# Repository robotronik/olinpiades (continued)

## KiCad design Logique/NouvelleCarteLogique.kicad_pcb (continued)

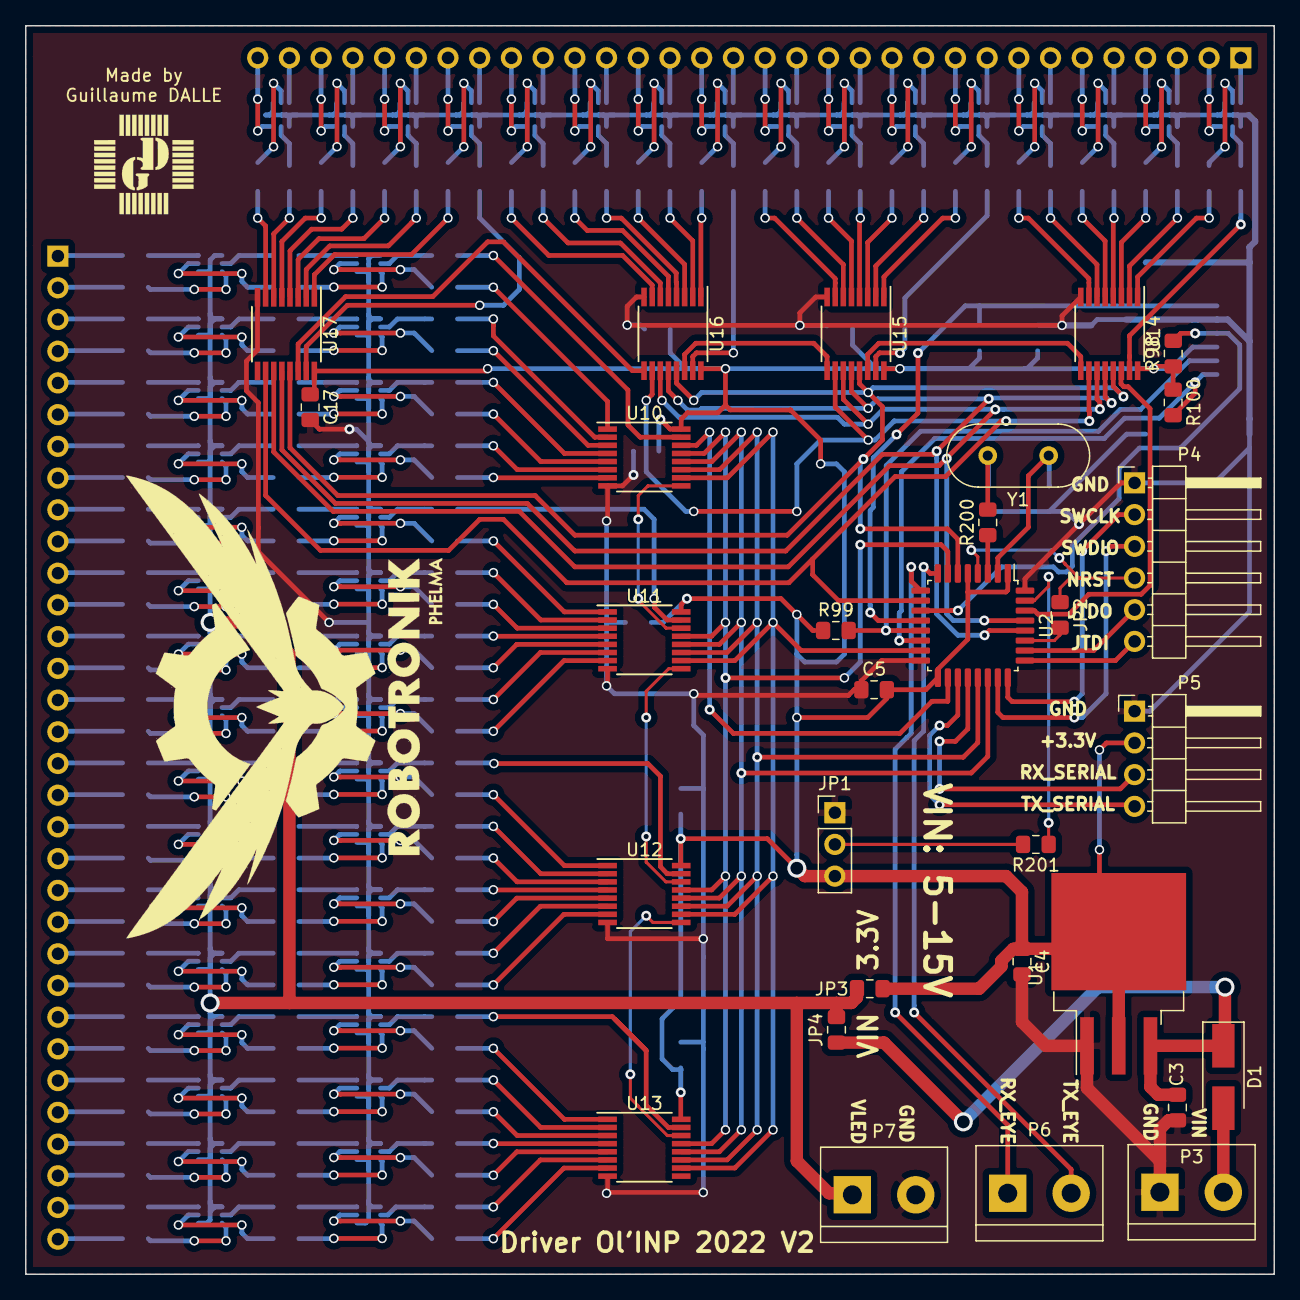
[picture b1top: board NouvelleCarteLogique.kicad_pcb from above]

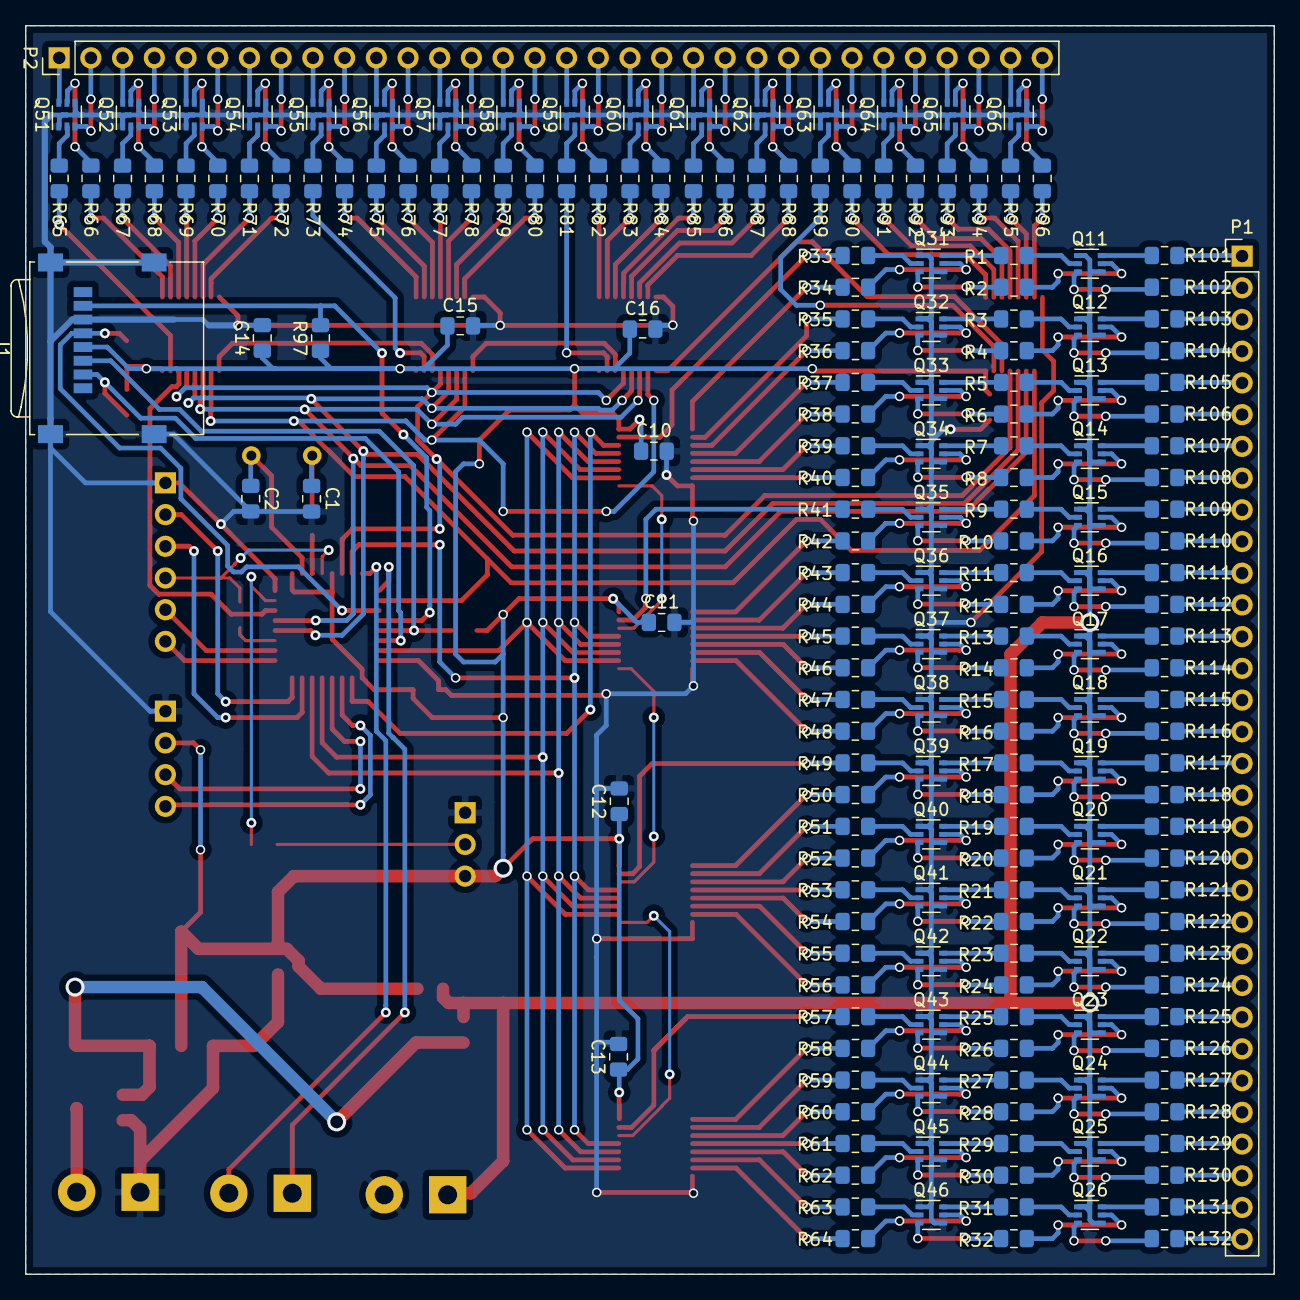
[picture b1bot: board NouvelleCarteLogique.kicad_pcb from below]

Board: 2 copper layers, 100.0 x 100.0 mm, 219 parts (189 on the bottom side), 328 nets.

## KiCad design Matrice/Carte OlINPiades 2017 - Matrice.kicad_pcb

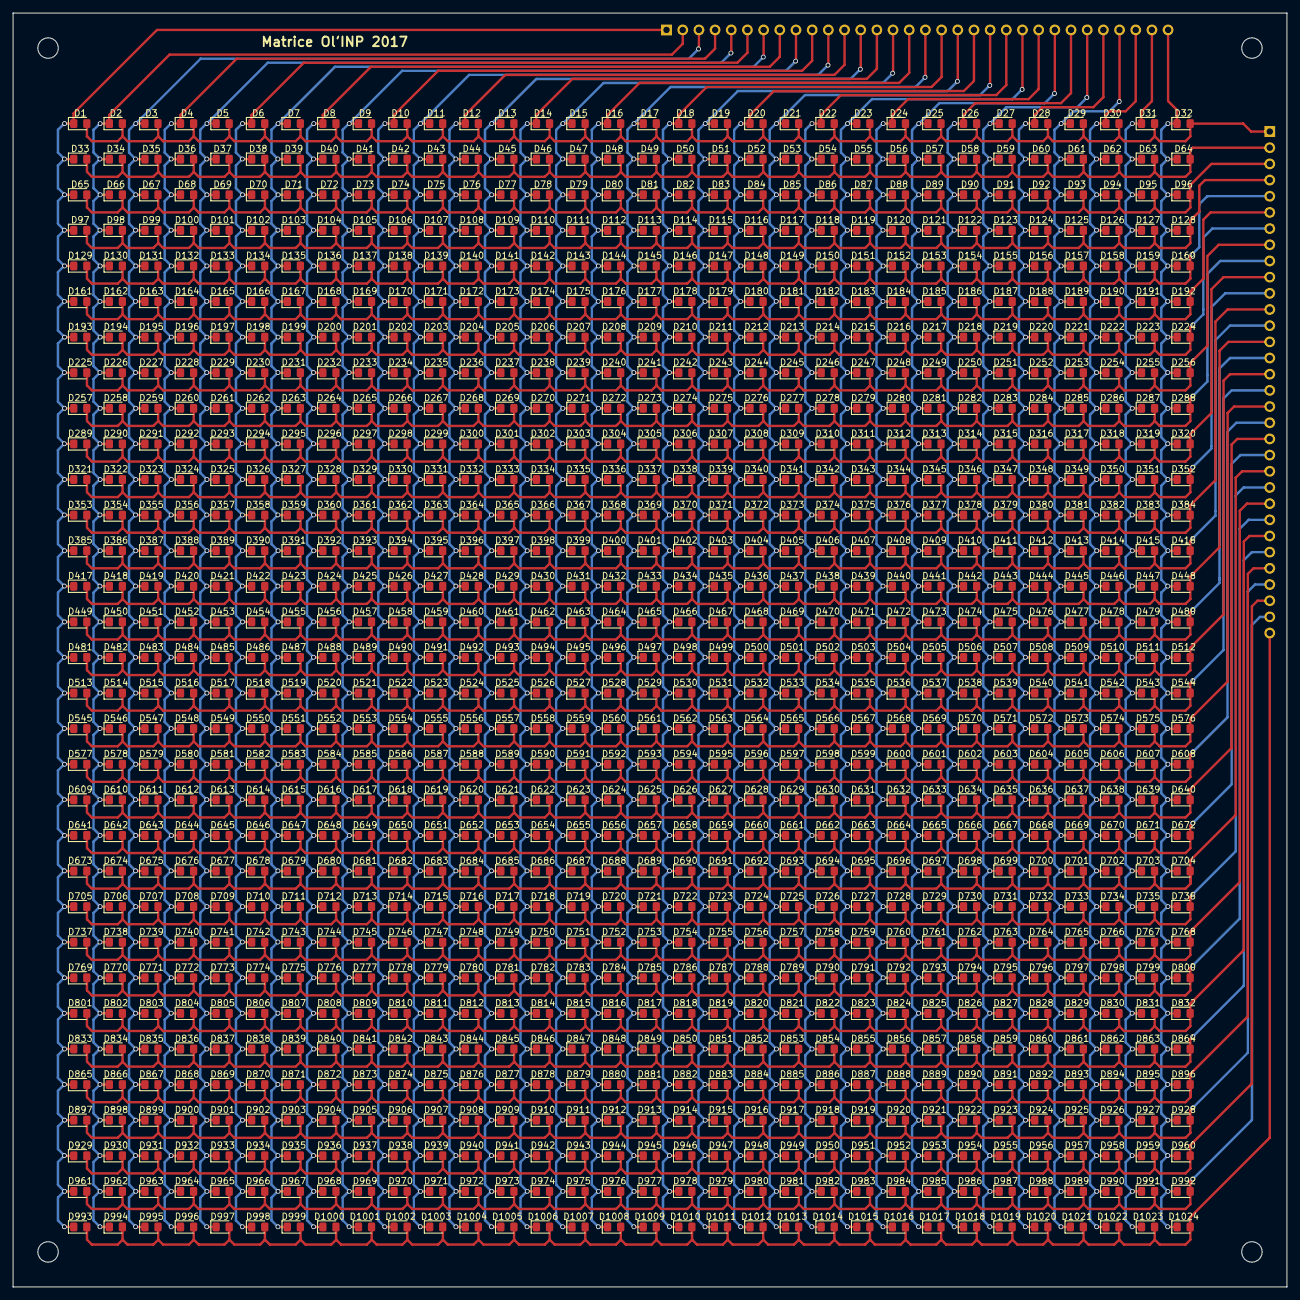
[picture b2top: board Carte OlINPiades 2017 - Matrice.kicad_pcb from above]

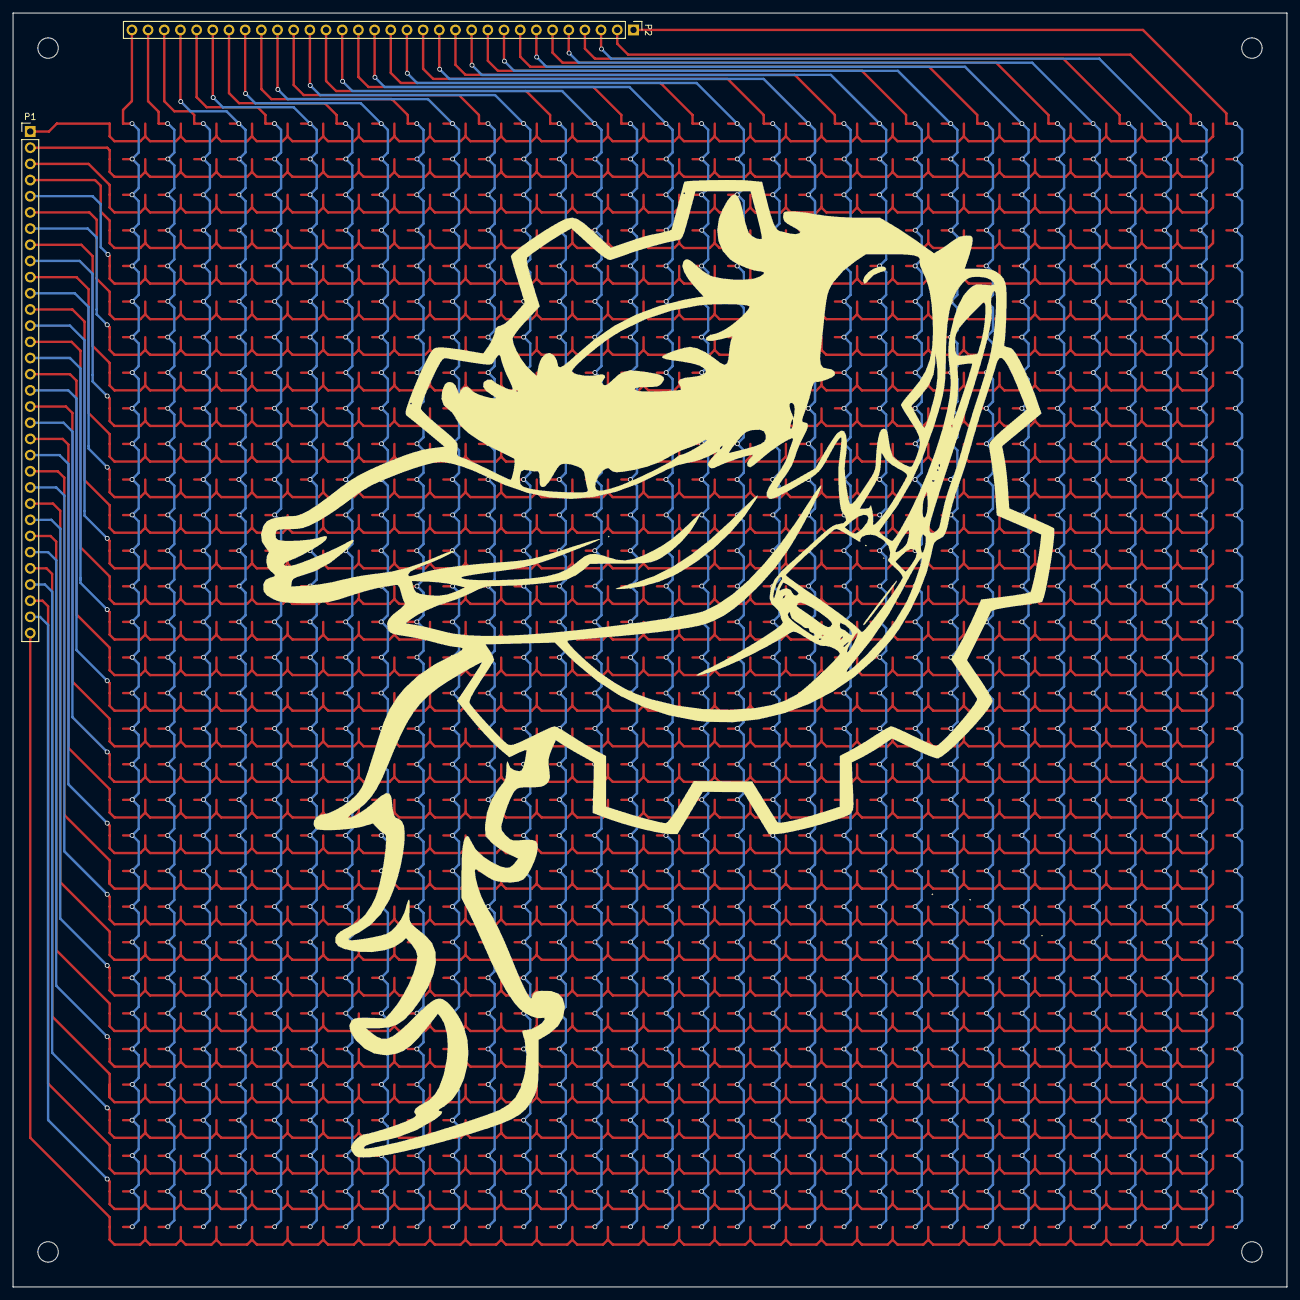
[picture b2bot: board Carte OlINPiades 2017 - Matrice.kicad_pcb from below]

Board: 2 copper layers, 200.0 x 200.0 mm, 1031 parts (3 on the bottom side), 64 nets.

Parts:
D1, D2, D3, D4, D5, D6, D7, D8, D9, D10, D11, D12, D13, D14, D15, D16, D17, D18, D19, D20, D21, D22, D23, D24, D25, D26, D27, D28, D29, D30, D31, D32, D33, D34, D35, D36, D37, D38, D39, D40, D41, D42, D43, D44, D45, D46, D47, D48, D49, D50, D51, D52, D53, D54, D55, D56, D57, D58, D59, D60, D61, D62, D63, D64, D65, D66, D67, D68, D69, D70, D71, D72, D73, D74, D75, D76, D77, D78, D79, D80, D81, D82, D83, D84, D85, D86, D87, D88, D89, D90, D91, D92, D93, D94, D95, D96, D97, D98, D99, D100, D101, D102, D103, D104, D105, D106, D107, D108, D109, D110, D111, D112, D113, D114, D115, D116, D117, D118, D119, D120, D121, D122, D123, D124, D125, D126, D127, D128, D129, D130, D131, D132, D133, D134, D135, D136, D137, D138, D139, D140, D141, D142, D143, D144, D145, D146, D147, D148, D149, D150, D151, D152, D153, D154, D155, D156, D157, D158, D159, D160, D161, D162, D163, D164, D165, D166, D167, D168, D169, D170, D171, D172, D173, D174, D175, D176, D177, D178, D179, D180, D181, D182, D183, D184, D185, D186, D187, D188, D189, D190, D191, D192, D193, D194, D195, D196, D197, D198, D199, D200, D201, D202, D203, D204, D205, D206, D207, D208, D209, D210, D211, D212, D213, D214, D215, D216, D217, D218, D219, D220, D221, D222, D223, D224, D225, D226, D227, D228, D229, D230, D231, D232, D233, D234, D235, D236, D237, D238, D239, D240, D241, D242, D243, D244, D245, D246, D247, D248, D249, D250, D251, D252, D253, D254, D255, D256, D257, D258, D259, D260, D261, D262, D263, D264, D265, D266, D267, D268, D269, D270, D271, D272, D273, D274, D275, D276, D277, D278, D279, D280, D281, D282, D283, D284, D285, D286, D287, D288, D289, D290, D291, D292, D293, D294, D295, D296, D297, D298, D299, D300, D301, D302, D303, D304, D305, D306, D307, D308, D309, D310, D311, D312, D313, D314, D315, D316, D317, D318, D319, D320, D321, D322, D323, D324, D325, D326, D327, D328, D329, D330, D331, D332, D333, D334, D335, D336, D337, D338, D339, D340, D341, D342, D343, D344, D345, D346, D347, D348, D349, D350, D351, D352, D353, D354, D355, D356, D357, D358, D359, D360, D361, D362, D363, D364, D365, D366, D367, D368, D369, D370, D371, D372, D373, D374, D375, D376, D377, D378, D379, D380, D381, D382, D383, D384, D385, D386, D387, D388, D389, D390, D391, D392, D393, D394, D395, D396, D397, D398, D399, D400, D401, D402, D403, D404, D405, D406, D407, D408, D409, D410, D411, D412, D413, D414, D415, D416, D417, D418, D419, D420, D421, D422, D423, D424, D425, D426, D427, D428, D429, D430, D431, D432, D433, D434, D435, D436, D437, D438, D439, D440, D441, D442, D443, D444, D445, D446, D447, D448, D449, D450, D451, D452, D453, D454, D455, D456, D457, D458, D459, D460, D461, D462, D463, D464, D465, D466, D467, D468, D469, D470, D471, D472, D473, D474, D475, D476, D477, D478, D479, D480, D481, D482, D483, D484, D485, D486, D487, D488, D489, D490, D491, D492, D493, D494, D495, D496, D497, D498, D499, D500, D501, D502, D503, D504, D505, D506, D507, D508, D509, D510, D511, D512, D513, D514, D515, D516, D517, D518, D519, D520, D521, D522, D523, D524, D525, D526, D527, D528, D529, D530, D531, D532, D533, D534, D535, D536, D537, D538, D539, D540, D541, D542, D543, D544, D545, D546, D547, D548, D549, D550, D551, D552, D553, D554, D555, D556, D557, D558, D559, D560, D561, D562, D563, D564, D565, D566, D567, D568, D569, D570, D571, D572, D573, D574, D575, D576, D577, D578, D579, D580, D581, D582, D583, D584, D585, D586, D587, D588, D589, D590, D591, D592, D593, D594, D595, D596, D597, D598, D599, D600, D601, D602, D603, D604, D605, D606, D607, D608, D609, D610, D611, D612, D613, D614, D615, D616, D617, D618, D619, D620, D621, D622, D623, D624, D625, D626, D627, D628, D629, D630, D631, D632, D633, D634, D635, D636, D637, D638, D639, D640, D641, D642, D643, D644, D645, D646, D647, D648, D649, D650, D651, D652, D653, D654, D655, D656, D657, D658, D659, D660, D661, D662, D663, D664, D665, D666, D667, D668, D669, D670, D671, D672, D673, D674, D675, D676, D677, D678, D679, D680, D681, D682, D683, D684, D685, D686, D687, D688, D689, D690, D691, D692, D693, D694, D695, D696, D697, D698, D699, D700, D701, D702, D703, D704, D705, D706, D707, D708, D709, D710, D711, D712, D713, D714, D715, D716, D717, D718, D719, D720, D721, D722, D723, D724, D725, D726, D727, D728, D729, D730, D731, D732, D733, D734, D735, D736, D737, D738, D739, D740, D741, D742, D743, D744, D745, D746, D747, D748, D749, D750, D751, D752, D753, D754, D755, D756, D757, D758, D759, D760, D761, D762, D763, D764, D765, D766, D767, D768, D769, D770, D771, D772, D773, D774, D775, D776, D777, D778, D779, D780, D781, D782, D783, D784, D785, D786, D787, D788, D789, D790, D791, D792, D793, D794, D795, D796, D797, D798, D799, D800, D801, D802, D803, D804, D805, D806, D807, D808, D809, D810, D811, D812, D813, D814, D815, D816, D817, D818, D819, D820, D821, D822, D823, D824, D825, D826, D827, D828, D829, D830, D831, D832, D833, D834, D835, D836, D837, D838, D839, D840, D841, D842, D843, D844, D845, D846, D847, D848, D849, D850, D851, D852, D853, D854, D855, D856, D857, D858, D859, D860, D861, D862, D863, D864, D865, D866, D867, D868, D869, D870, D871, D872, D873, D874, D875, D876, D877, D878, D879, D880, D881, D882, D883, D884, D885, D886, D887, D888, D889, D890, D891, D892, D893, D894, D895, D896, D897, D898, D899, D900, D901, D902, D903, D904, D905, D906, D907, D908, D909, D910, D911, D912, D913, D914, D915, D916, D917, D918, D919, D920, D921, D922, D923, D924, D925, D926, D927, D928, D929, D930, D931, D932, D933, D934, D935, D936, D937, D938, D939, D940, D941, D942, D943, D944, D945, D946, D947, D948, D949, D950, D951, D952, D953, D954, D955, D956, D957, D958, D959, D960, D961, D962, D963, D964, D965, D966, D967, D968, D969, D970, D971, D972, D973, D974, D975, D976, D977, D978, D979, D980, D981, D982, D983, D984, D985, D986, D987, D988, D989, D990, D991, D992, D993, D994, D995, D996, D997, D998, D999, D1000, D1001, D1002, D1003, D1004, D1005, D1006, D1007, D1008, D1009, D1010, D1011, D1012, D1013, D1014, D1015, D1016, D1017, D1018, D1019, D1020, D1021, D1022, D1023, D1024: LED; LED_0805_2012Metric_Pad1.15x1.40mm_HandSolder
LOGO1: Logo_Open_Hardware_Small; robotronik_logo_big
P1, P2: CONN_01X32; PinHeader_1x32_P2.54mm_Vertical
PAD1, PAD2, PAD3, PAD4: MountingHole; MountingHole_3.2mm_M3

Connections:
unnamed: D1.1, D33.1, D65.1, D97.1, D129.1, D161.1, D193.1, D225.1, D257.1, D289.1, D321.1, D353.1, D385.1, D417.1, D449.1, D481.1, D513.1, D545.1, D577.1, D609.1, D641.1, D673.1, D705.1, D737.1, D769.1, D801.1, D833.1, D865.1, D897.1, D929.1, D961.1, D993.1, P2.1
unnamed: D1.2, D2.2, D3.2, D4.2, D5.2, D6.2, D7.2, D8.2, D9.2, D10.2, D11.2, D12.2, D13.2, D14.2, D15.2, D16.2, D17.2, D18.2, D19.2, D20.2, D21.2, D22.2, D23.2, D24.2, D25.2, D26.2, D27.2, D28.2, D29.2, D30.2, D31.2, D32.2, P1.1
unnamed: D10.1, D42.1, D74.1, D106.1, D138.1, D170.1, D202.1, D234.1, D266.1, D298.1, D330.1, D362.1, D394.1, D426.1, D458.1, D490.1, D522.1, D554.1, D586.1, D618.1, D650.1, D682.1, D714.1, D746.1, D778.1, D810.1, D842.1, D874.1, D906.1, D938.1, D970.1, D1002.1, P2.10
unnamed: D33.2, D34.2, D35.2, D36.2, D37.2, D38.2, D39.2, D40.2, D41.2, D42.2, D43.2, D44.2, D45.2, D46.2, D47.2, D48.2, D49.2, D50.2, D51.2, D52.2, D53.2, D54.2, D55.2, D56.2, D57.2, D58.2, D59.2, D60.2, D61.2, D62.2, D63.2, D64.2, P1.2
unnamed: D65.2, D66.2, D67.2, D68.2, D69.2, D70.2, D71.2, D72.2, D73.2, D74.2, D75.2, D76.2, D77.2, D78.2, D79.2, D80.2, D81.2, D82.2, D83.2, D84.2, D85.2, D86.2, D87.2, D88.2, D89.2, D90.2, D91.2, D92.2, D93.2, D94.2, D95.2, D96.2, P1.3
unnamed: D4.1, D36.1, D68.1, D100.1, D132.1, D164.1, D196.1, D228.1, D260.1, D292.1, D324.1, D356.1, D388.1, D420.1, D452.1, D484.1, D516.1, D548.1, D580.1, D612.1, D644.1, D676.1, D708.1, D740.1, D772.1, D804.1, D836.1, D868.1, D900.1, D932.1, D964.1, D996.1, P2.4
unnamed: D97.2, D98.2, D99.2, D100.2, D101.2, D102.2, D103.2, D104.2, D105.2, D106.2, D107.2, D108.2, D109.2, D110.2, D111.2, D112.2, D113.2, D114.2, D115.2, D116.2, D117.2, D118.2, D119.2, D120.2, D121.2, D122.2, D123.2, D124.2, D125.2, D126.2, D127.2, D128.2, P1.4
unnamed: D5.1, D37.1, D69.1, D101.1, D133.1, D165.1, D197.1, D229.1, D261.1, D293.1, D325.1, D357.1, D389.1, D421.1, D453.1, D485.1, D517.1, D549.1, D581.1, D613.1, D645.1, D677.1, D709.1, D741.1, D773.1, D805.1, D837.1, D869.1, D901.1, D933.1, D965.1, D997.1, P2.5
unnamed: D6.1, D38.1, D70.1, D102.1, D134.1, D166.1, D198.1, D230.1, D262.1, D294.1, D326.1, D358.1, D390.1, D422.1, D454.1, D486.1, D518.1, D550.1, D582.1, D614.1, D646.1, D678.1, D710.1, D742.1, D774.1, D806.1, D838.1, D870.1, D902.1, D934.1, D966.1, D998.1, P2.6
unnamed: D7.1, D39.1, D71.1, D103.1, D135.1, D167.1, D199.1, D231.1, D263.1, D295.1, D327.1, D359.1, D391.1, D423.1, D455.1, D487.1, D519.1, D551.1, D583.1, D615.1, D647.1, D679.1, D711.1, D743.1, D775.1, D807.1, D839.1, D871.1, D903.1, D935.1, D967.1, D999.1, P2.7
unnamed: D129.2, D130.2, D131.2, D132.2, D133.2, D134.2, D135.2, D136.2, D137.2, D138.2, D139.2, D140.2, D141.2, D142.2, D143.2, D144.2, D145.2, D146.2, D147.2, D148.2, D149.2, D150.2, D151.2, D152.2, D153.2, D154.2, D155.2, D156.2, D157.2, D158.2, D159.2, D160.2, P1.5
unnamed: D2.1, D34.1, D66.1, D98.1, D130.1, D162.1, D194.1, D226.1, D258.1, D290.1, D322.1, D354.1, D386.1, D418.1, D450.1, D482.1, D514.1, D546.1, D578.1, D610.1, D642.1, D674.1, D706.1, D738.1, D770.1, D802.1, D834.1, D866.1, D898.1, D930.1, D962.1, D994.1, P2.2
unnamed: D3.1, D35.1, D67.1, D99.1, D131.1, D163.1, D195.1, D227.1, D259.1, D291.1, D323.1, D355.1, D387.1, D419.1, D451.1, D483.1, D515.1, D547.1, D579.1, D611.1, D643.1, D675.1, D707.1, D739.1, D771.1, D803.1, D835.1, D867.1, D899.1, D931.1, D963.1, D995.1, P2.3
unnamed: D161.2, D162.2, D163.2, D164.2, D165.2, D166.2, D167.2, D168.2, D169.2, D170.2, D171.2, D172.2, D173.2, D174.2, D175.2, D176.2, D177.2, D178.2, D179.2, D180.2, D181.2, D182.2, D183.2, D184.2, D185.2, D186.2, D187.2, D188.2, D189.2, D190.2, D191.2, D192.2, P1.6
unnamed: D193.2, D194.2, D195.2, D196.2, D197.2, D198.2, D199.2, D200.2, D201.2, D202.2, D203.2, D204.2, D205.2, D206.2, D207.2, D208.2, D209.2, D210.2, D211.2, D212.2, D213.2, D214.2, D215.2, D216.2, D217.2, D218.2, D219.2, D220.2, D221.2, D222.2, D223.2, D224.2, P1.7
unnamed: D225.2, D226.2, D227.2, D228.2, D229.2, D230.2, D231.2, D232.2, D233.2, D234.2, D235.2, D236.2, D237.2, D238.2, D239.2, D240.2, D241.2, D242.2, D243.2, D244.2, D245.2, D246.2, D247.2, D248.2, D249.2, D250.2, D251.2, D252.2, D253.2, D254.2, D255.2, D256.2, P1.8
unnamed: D257.2, D258.2, D259.2, D260.2, D261.2, D262.2, D263.2, D264.2, D265.2, D266.2, D267.2, D268.2, D269.2, D270.2, D271.2, D272.2, D273.2, D274.2, D275.2, D276.2, D277.2, D278.2, D279.2, D280.2, D281.2, D282.2, D283.2, D284.2, D285.2, D286.2, D287.2, D288.2, P1.9
unnamed: D289.2, D290.2, D291.2, D292.2, D293.2, D294.2, D295.2, D296.2, D297.2, D298.2, D299.2, D300.2, D301.2, D302.2, D303.2, D304.2, D305.2, D306.2, D307.2, D308.2, D309.2, D310.2, D311.2, D312.2, D313.2, D314.2, D315.2, D316.2, D317.2, D318.2, D319.2, D320.2, P1.10
unnamed: D321.2, D322.2, D323.2, D324.2, D325.2, D326.2, D327.2, D328.2, D329.2, D330.2, D331.2, D332.2, D333.2, D334.2, D335.2, D336.2, D337.2, D338.2, D339.2, D340.2, D341.2, D342.2, D343.2, D344.2, D345.2, D346.2, D347.2, D348.2, D349.2, D350.2, D351.2, D352.2, P1.11
unnamed: D353.2, D354.2, D355.2, D356.2, D357.2, D358.2, D359.2, D360.2, D361.2, D362.2, D363.2, D364.2, D365.2, D366.2, D367.2, D368.2, D369.2, D370.2, D371.2, D372.2, D373.2, D374.2, D375.2, D376.2, D377.2, D378.2, D379.2, D380.2, D381.2, D382.2, D383.2, D384.2, P1.12
unnamed: D385.2, D386.2, D387.2, D388.2, D389.2, D390.2, D391.2, D392.2, D393.2, D394.2, D395.2, D396.2, D397.2, D398.2, D399.2, D400.2, D401.2, D402.2, D403.2, D404.2, D405.2, D406.2, D407.2, D408.2, D409.2, D410.2, D411.2, D412.2, D413.2, D414.2, D415.2, D416.2, P1.13
unnamed: D417.2, D418.2, D419.2, D420.2, D421.2, D422.2, D423.2, D424.2, D425.2, D426.2, D427.2, D428.2, D429.2, D430.2, D431.2, D432.2, D433.2, D434.2, D435.2, D436.2, D437.2, D438.2, D439.2, D440.2, D441.2, D442.2, D443.2, D444.2, D445.2, D446.2, D447.2, D448.2, P1.14
unnamed: D449.2, D450.2, D451.2, D452.2, D453.2, D454.2, D455.2, D456.2, D457.2, D458.2, D459.2, D460.2, D461.2, D462.2, D463.2, D464.2, D465.2, D466.2, D467.2, D468.2, D469.2, D470.2, D471.2, D472.2, D473.2, D474.2, D475.2, D476.2, D477.2, D478.2, D479.2, D480.2, P1.15
unnamed: D481.2, D482.2, D483.2, D484.2, D485.2, D486.2, D487.2, D488.2, D489.2, D490.2, D491.2, D492.2, D493.2, D494.2, D495.2, D496.2, D497.2, D498.2, D499.2, D500.2, D501.2, D502.2, D503.2, D504.2, D505.2, D506.2, D507.2, D508.2, D509.2, D510.2, D511.2, D512.2, P1.16
unnamed: D513.2, D514.2, D515.2, D516.2, D517.2, D518.2, D519.2, D520.2, D521.2, D522.2, D523.2, D524.2, D525.2, D526.2, D527.2, D528.2, D529.2, D530.2, D531.2, D532.2, D533.2, D534.2, D535.2, D536.2, D537.2, D538.2, D539.2, D540.2, D541.2, D542.2, D543.2, D544.2, P1.17
unnamed: D545.2, D546.2, D547.2, D548.2, D549.2, D550.2, D551.2, D552.2, D553.2, D554.2, D555.2, D556.2, D557.2, D558.2, D559.2, D560.2, D561.2, D562.2, D563.2, D564.2, D565.2, D566.2, D567.2, D568.2, D569.2, D570.2, D571.2, D572.2, D573.2, D574.2, D575.2, D576.2, P1.18
unnamed: D577.2, D578.2, D579.2, D580.2, D581.2, D582.2, D583.2, D584.2, D585.2, D586.2, D587.2, D588.2, D589.2, D590.2, D591.2, D592.2, D593.2, D594.2, D595.2, D596.2, D597.2, D598.2, D599.2, D600.2, D601.2, D602.2, D603.2, D604.2, D605.2, D606.2, D607.2, D608.2, P1.19
unnamed: D609.2, D610.2, D611.2, D612.2, D613.2, D614.2, D615.2, D616.2, D617.2, D618.2, D619.2, D620.2, D621.2, D622.2, D623.2, D624.2, D625.2, D626.2, D627.2, D628.2, D629.2, D630.2, D631.2, D632.2, D633.2, D634.2, D635.2, D636.2, D637.2, D638.2, D639.2, D640.2, P1.20
unnamed: D641.2, D642.2, D643.2, D644.2, D645.2, D646.2, D647.2, D648.2, D649.2, D650.2, D651.2, D652.2, D653.2, D654.2, D655.2, D656.2, D657.2, D658.2, D659.2, D660.2, D661.2, D662.2, D663.2, D664.2, D665.2, D666.2, D667.2, D668.2, D669.2, D670.2, D671.2, D672.2, P1.21
unnamed: D673.2, D674.2, D675.2, D676.2, D677.2, D678.2, D679.2, D680.2, D681.2, D682.2, D683.2, D684.2, D685.2, D686.2, D687.2, D688.2, D689.2, D690.2, D691.2, D692.2, D693.2, D694.2, D695.2, D696.2, D697.2, D698.2, D699.2, D700.2, D701.2, D702.2, D703.2, D704.2, P1.22
unnamed: D705.2, D706.2, D707.2, D708.2, D709.2, D710.2, D711.2, D712.2, D713.2, D714.2, D715.2, D716.2, D717.2, D718.2, D719.2, D720.2, D721.2, D722.2, D723.2, D724.2, D725.2, D726.2, D727.2, D728.2, D729.2, D730.2, D731.2, D732.2, D733.2, D734.2, D735.2, D736.2, P1.23
unnamed: D737.2, D738.2, D739.2, D740.2, D741.2, D742.2, D743.2, D744.2, D745.2, D746.2, D747.2, D748.2, D749.2, D750.2, D751.2, D752.2, D753.2, D754.2, D755.2, D756.2, D757.2, D758.2, D759.2, D760.2, D761.2, D762.2, D763.2, D764.2, D765.2, D766.2, D767.2, D768.2, P1.24
unnamed: D769.2, D770.2, D771.2, D772.2, D773.2, D774.2, D775.2, D776.2, D777.2, D778.2, D779.2, D780.2, D781.2, D782.2, D783.2, D784.2, D785.2, D786.2, D787.2, D788.2, D789.2, D790.2, D791.2, D792.2, D793.2, D794.2, D795.2, D796.2, D797.2, D798.2, D799.2, D800.2, P1.25
unnamed: D801.2, D802.2, D803.2, D804.2, D805.2, D806.2, D807.2, D808.2, D809.2, D810.2, D811.2, D812.2, D813.2, D814.2, D815.2, D816.2, D817.2, D818.2, D819.2, D820.2, D821.2, D822.2, D823.2, D824.2, D825.2, D826.2, D827.2, D828.2, D829.2, D830.2, D831.2, D832.2, P1.26
unnamed: D833.2, D834.2, D835.2, D836.2, D837.2, D838.2, D839.2, D840.2, D841.2, D842.2, D843.2, D844.2, D845.2, D846.2, D847.2, D848.2, D849.2, D850.2, D851.2, D852.2, D853.2, D854.2, D855.2, D856.2, D857.2, D858.2, D859.2, D860.2, D861.2, D862.2, D863.2, D864.2, P1.27
unnamed: D865.2, D866.2, D867.2, D868.2, D869.2, D870.2, D871.2, D872.2, D873.2, D874.2, D875.2, D876.2, D877.2, D878.2, D879.2, D880.2, D881.2, D882.2, D883.2, D884.2, D885.2, D886.2, D887.2, D888.2, D889.2, D890.2, D891.2, D892.2, D893.2, D894.2, D895.2, D896.2, P1.28
unnamed: D897.2, D898.2, D899.2, D900.2, D901.2, D902.2, D903.2, D904.2, D905.2, D906.2, D907.2, D908.2, D909.2, D910.2, D911.2, D912.2, D913.2, D914.2, D915.2, D916.2, D917.2, D918.2, D919.2, D920.2, D921.2, D922.2, D923.2, D924.2, D925.2, D926.2, D927.2, D928.2, P1.29
unnamed: D929.2, D930.2, D931.2, D932.2, D933.2, D934.2, D935.2, D936.2, D937.2, D938.2, D939.2, D940.2, D941.2, D942.2, D943.2, D944.2, D945.2, D946.2, D947.2, D948.2, D949.2, D950.2, D951.2, D952.2, D953.2, D954.2, D955.2, D956.2, D957.2, D958.2, D959.2, D960.2, P1.30
unnamed: D961.2, D962.2, D963.2, D964.2, D965.2, D966.2, D967.2, D968.2, D969.2, D970.2, D971.2, D972.2, D973.2, D974.2, D975.2, D976.2, D977.2, D978.2, D979.2, D980.2, D981.2, D982.2, D983.2, D984.2, D985.2, D986.2, D987.2, D988.2, D989.2, D990.2, D991.2, D992.2, P1.31
unnamed: D8.1, D40.1, D72.1, D104.1, D136.1, D168.1, D200.1, D232.1, D264.1, D296.1, D328.1, D360.1, D392.1, D424.1, D456.1, D488.1, D520.1, D552.1, D584.1, D616.1, D648.1, D680.1, D712.1, D744.1, D776.1, D808.1, D840.1, D872.1, D904.1, D936.1, D968.1, D1000.1, P2.8
unnamed: D993.2, D994.2, D995.2, D996.2, D997.2, D998.2, D999.2, D1000.2, D1001.2, D1002.2, D1003.2, D1004.2, D1005.2, D1006.2, D1007.2, D1008.2, D1009.2, D1010.2, D1011.2, D1012.2, D1013.2, D1014.2, D1015.2, D1016.2, D1017.2, D1018.2, D1019.2, D1020.2, D1021.2, D1022.2, D1023.2, D1024.2, P1.32
unnamed: D9.1, D41.1, D73.1, D105.1, D137.1, D169.1, D201.1, D233.1, D265.1, D297.1, D329.1, D361.1, D393.1, D425.1, D457.1, D489.1, D521.1, D553.1, D585.1, D617.1, D649.1, D681.1, D713.1, D745.1, D777.1, D809.1, D841.1, D873.1, D905.1, D937.1, D969.1, D1001.1, P2.9
unnamed: D11.1, D43.1, D75.1, D107.1, D139.1, D171.1, D203.1, D235.1, D267.1, D299.1, D331.1, D363.1, D395.1, D427.1, D459.1, D491.1, D523.1, D555.1, D587.1, D619.1, D651.1, D683.1, D715.1, D747.1, D779.1, D811.1, D843.1, D875.1, D907.1, D939.1, D971.1, D1003.1, P2.11
unnamed: D12.1, D44.1, D76.1, D108.1, D140.1, D172.1, D204.1, D236.1, D268.1, D300.1, D332.1, D364.1, D396.1, D428.1, D460.1, D492.1, D524.1, D556.1, D588.1, D620.1, D652.1, D684.1, D716.1, D748.1, D780.1, D812.1, D844.1, D876.1, D908.1, D940.1, D972.1, D1004.1, P2.12
unnamed: D13.1, D45.1, D77.1, D109.1, D141.1, D173.1, D205.1, D237.1, D269.1, D301.1, D333.1, D365.1, D397.1, D429.1, D461.1, D493.1, D525.1, D557.1, D589.1, D621.1, D653.1, D685.1, D717.1, D749.1, D781.1, D813.1, D845.1, D877.1, D909.1, D941.1, D973.1, D1005.1, P2.13
unnamed: D14.1, D46.1, D78.1, D110.1, D142.1, D174.1, D206.1, D238.1, D270.1, D302.1, D334.1, D366.1, D398.1, D430.1, D462.1, D494.1, D526.1, D558.1, D590.1, D622.1, D654.1, D686.1, D718.1, D750.1, D782.1, D814.1, D846.1, D878.1, D910.1, D942.1, D974.1, D1006.1, P2.14
unnamed: D15.1, D47.1, D79.1, D111.1, D143.1, D175.1, D207.1, D239.1, D271.1, D303.1, D335.1, D367.1, D399.1, D431.1, D463.1, D495.1, D527.1, D559.1, D591.1, D623.1, D655.1, D687.1, D719.1, D751.1, D783.1, D815.1, D847.1, D879.1, D911.1, D943.1, D975.1, D1007.1, P2.15
unnamed: D16.1, D48.1, D80.1, D112.1, D144.1, D176.1, D208.1, D240.1, D272.1, D304.1, D336.1, D368.1, D400.1, D432.1, D464.1, D496.1, D528.1, D560.1, D592.1, D624.1, D656.1, D688.1, D720.1, D752.1, D784.1, D816.1, D848.1, D880.1, D912.1, D944.1, D976.1, D1008.1, P2.16
unnamed: D17.1, D49.1, D81.1, D113.1, D145.1, D177.1, D209.1, D241.1, D273.1, D305.1, D337.1, D369.1, D401.1, D433.1, D465.1, D497.1, D529.1, D561.1, D593.1, D625.1, D657.1, D689.1, D721.1, D753.1, D785.1, D817.1, D849.1, D881.1, D913.1, D945.1, D977.1, D1009.1, P2.17
unnamed: D18.1, D50.1, D82.1, D114.1, D146.1, D178.1, D210.1, D242.1, D274.1, D306.1, D338.1, D370.1, D402.1, D434.1, D466.1, D498.1, D530.1, D562.1, D594.1, D626.1, D658.1, D690.1, D722.1, D754.1, D786.1, D818.1, D850.1, D882.1, D914.1, D946.1, D978.1, D1010.1, P2.18
unnamed: D19.1, D51.1, D83.1, D115.1, D147.1, D179.1, D211.1, D243.1, D275.1, D307.1, D339.1, D371.1, D403.1, D435.1, D467.1, D499.1, D531.1, D563.1, D595.1, D627.1, D659.1, D691.1, D723.1, D755.1, D787.1, D819.1, D851.1, D883.1, D915.1, D947.1, D979.1, D1011.1, P2.19
unnamed: D20.1, D52.1, D84.1, D116.1, D148.1, D180.1, D212.1, D244.1, D276.1, D308.1, D340.1, D372.1, D404.1, D436.1, D468.1, D500.1, D532.1, D564.1, D596.1, D628.1, D660.1, D692.1, D724.1, D756.1, D788.1, D820.1, D852.1, D884.1, D916.1, D948.1, D980.1, D1012.1, P2.20
unnamed: D21.1, D53.1, D85.1, D117.1, D149.1, D181.1, D213.1, D245.1, D277.1, D309.1, D341.1, D373.1, D405.1, D437.1, D469.1, D501.1, D533.1, D565.1, D597.1, D629.1, D661.1, D693.1, D725.1, D757.1, D789.1, D821.1, D853.1, D885.1, D917.1, D949.1, D981.1, D1013.1, P2.21
unnamed: D22.1, D54.1, D86.1, D118.1, D150.1, D182.1, D214.1, D246.1, D278.1, D310.1, D342.1, D374.1, D406.1, D438.1, D470.1, D502.1, D534.1, D566.1, D598.1, D630.1, D662.1, D694.1, D726.1, D758.1, D790.1, D822.1, D854.1, D886.1, D918.1, D950.1, D982.1, D1014.1, P2.22
unnamed: D23.1, D55.1, D87.1, D119.1, D151.1, D183.1, D215.1, D247.1, D279.1, D311.1, D343.1, D375.1, D407.1, D439.1, D471.1, D503.1, D535.1, D567.1, D599.1, D631.1, D663.1, D695.1, D727.1, D759.1, D791.1, D823.1, D855.1, D887.1, D919.1, D951.1, D983.1, D1015.1, P2.23
unnamed: D24.1, D56.1, D88.1, D120.1, D152.1, D184.1, D216.1, D248.1, D280.1, D312.1, D344.1, D376.1, D408.1, D440.1, D472.1, D504.1, D536.1, D568.1, D600.1, D632.1, D664.1, D696.1, D728.1, D760.1, D792.1, D824.1, D856.1, D888.1, D920.1, D952.1, D984.1, D1016.1, P2.24
unnamed: D25.1, D57.1, D89.1, D121.1, D153.1, D185.1, D217.1, D249.1, D281.1, D313.1, D345.1, D377.1, D409.1, D441.1, D473.1, D505.1, D537.1, D569.1, D601.1, D633.1, D665.1, D697.1, D729.1, D761.1, D793.1, D825.1, D857.1, D889.1, D921.1, D953.1, D985.1, D1017.1, P2.25
unnamed: D26.1, D58.1, D90.1, D122.1, D154.1, D186.1, D218.1, D250.1, D282.1, D314.1, D346.1, D378.1, D410.1, D442.1, D474.1, D506.1, D538.1, D570.1, D602.1, D634.1, D666.1, D698.1, D730.1, D762.1, D794.1, D826.1, D858.1, D890.1, D922.1, D954.1, D986.1, D1018.1, P2.26
unnamed: D27.1, D59.1, D91.1, D123.1, D155.1, D187.1, D219.1, D251.1, D283.1, D315.1, D347.1, D379.1, D411.1, D443.1, D475.1, D507.1, D539.1, D571.1, D603.1, D635.1, D667.1, D699.1, D731.1, D763.1, D795.1, D827.1, D859.1, D891.1, D923.1, D955.1, D987.1, D1019.1, P2.27
unnamed: D28.1, D60.1, D92.1, D124.1, D156.1, D188.1, D220.1, D252.1, D284.1, D316.1, D348.1, D380.1, D412.1, D444.1, D476.1, D508.1, D540.1, D572.1, D604.1, D636.1, D668.1, D700.1, D732.1, D764.1, D796.1, D828.1, D860.1, D892.1, D924.1, D956.1, D988.1, D1020.1, P2.28
unnamed: D29.1, D61.1, D93.1, D125.1, D157.1, D189.1, D221.1, D253.1, D285.1, D317.1, D349.1, D381.1, D413.1, D445.1, D477.1, D509.1, D541.1, D573.1, D605.1, D637.1, D669.1, D701.1, D733.1, D765.1, D797.1, D829.1, D861.1, D893.1, D925.1, D957.1, D989.1, D1021.1, P2.29
unnamed: D30.1, D62.1, D94.1, D126.1, D158.1, D190.1, D222.1, D254.1, D286.1, D318.1, D350.1, D382.1, D414.1, D446.1, D478.1, D510.1, D542.1, D574.1, D606.1, D638.1, D670.1, D702.1, D734.1, D766.1, D798.1, D830.1, D862.1, D894.1, D926.1, D958.1, D990.1, D1022.1, P2.30
unnamed: D31.1, D63.1, D95.1, D127.1, D159.1, D191.1, D223.1, D255.1, D287.1, D319.1, D351.1, D383.1, D415.1, D447.1, D479.1, D511.1, D543.1, D575.1, D607.1, D639.1, D671.1, D703.1, D735.1, D767.1, D799.1, D831.1, D863.1, D895.1, D927.1, D959.1, D991.1, D1023.1, P2.31
unnamed: D32.1, D64.1, D96.1, D128.1, D160.1, D192.1, D224.1, D256.1, D288.1, D320.1, D352.1, D384.1, D416.1, D448.1, D480.1, D512.1, D544.1, D576.1, D608.1, D640.1, D672.1, D704.1, D736.1, D768.1, D800.1, D832.1, D864.1, D896.1, D928.1, D960.1, D992.1, D1024.1, P2.32
